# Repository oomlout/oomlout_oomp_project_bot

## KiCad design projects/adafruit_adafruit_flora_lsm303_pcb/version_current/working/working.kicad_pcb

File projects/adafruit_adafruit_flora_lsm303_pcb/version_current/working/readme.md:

# OOMP Project  
## Adafruit-Flora-LSM303-PCB  by adafruit  
  
oomp key: oomp_projects_flat_adafruit_adafruit_flora_lsm303_pcb  
(snippet of original readme)  
  
- Adafruit Flora LSM303 Sensor PCB  
<a href="http://www.adafruit.com/products/1247"><br/>  
Click here to purchase one from the Adafruit shop</a>  
  
Add motion and direction sensing to your wearable FLORA project with this high precision 3-axis Accelerometer+Compass sensor. Inside are two sensors, one is a classic 3-axis accelerometer, which can tell you which direction is down towards the Earth (by measuring gravity) or how fast the board is accelerating in 3D space. The other is a magnetometer that can sense where the strongest magnetic force is coming from, generally used to detect magnetic north. By combining this data you can then orient yourself.  
  
We based this sensor on the latest version of this popular sensor, the LSM303DLHC. The sensor has a digital (I2C) interface. Attaching it to the FLORA is simple: line up the sensor so its adjacent to the SDA/SCL pins and sew conductive thread from the 3V, SDA, SCL and GND pins. They line up perfectly so you will not have any crossed lines. You can only connect one of these sensors to your FLORA, but you can connect other I2C sensors/outputs by using the set of SCL/SDA pins on the opposite side.  
  
PCB files for Adafruit Flora LSM303 sensor. The format is EagleCAD schematic and board layout  
- https://www.adafruit.com/product/1247  
  
--- License  
  
Adafruit invests time and resources providing this open source design, please support Adafruit and open-source hardware by purchasing products   
  full source readme at [readme_src.md](readme_src.md)  
  
source repo at: [https://github.com/adafruit/Adafruit-Flora-LSM303-PCB](https://github.com/adafruit/Adafruit-Flora-LSM303-PCB)  
## Board  

## Schematic  

[schematic pdf](working_schematic.pdf)  
## Images

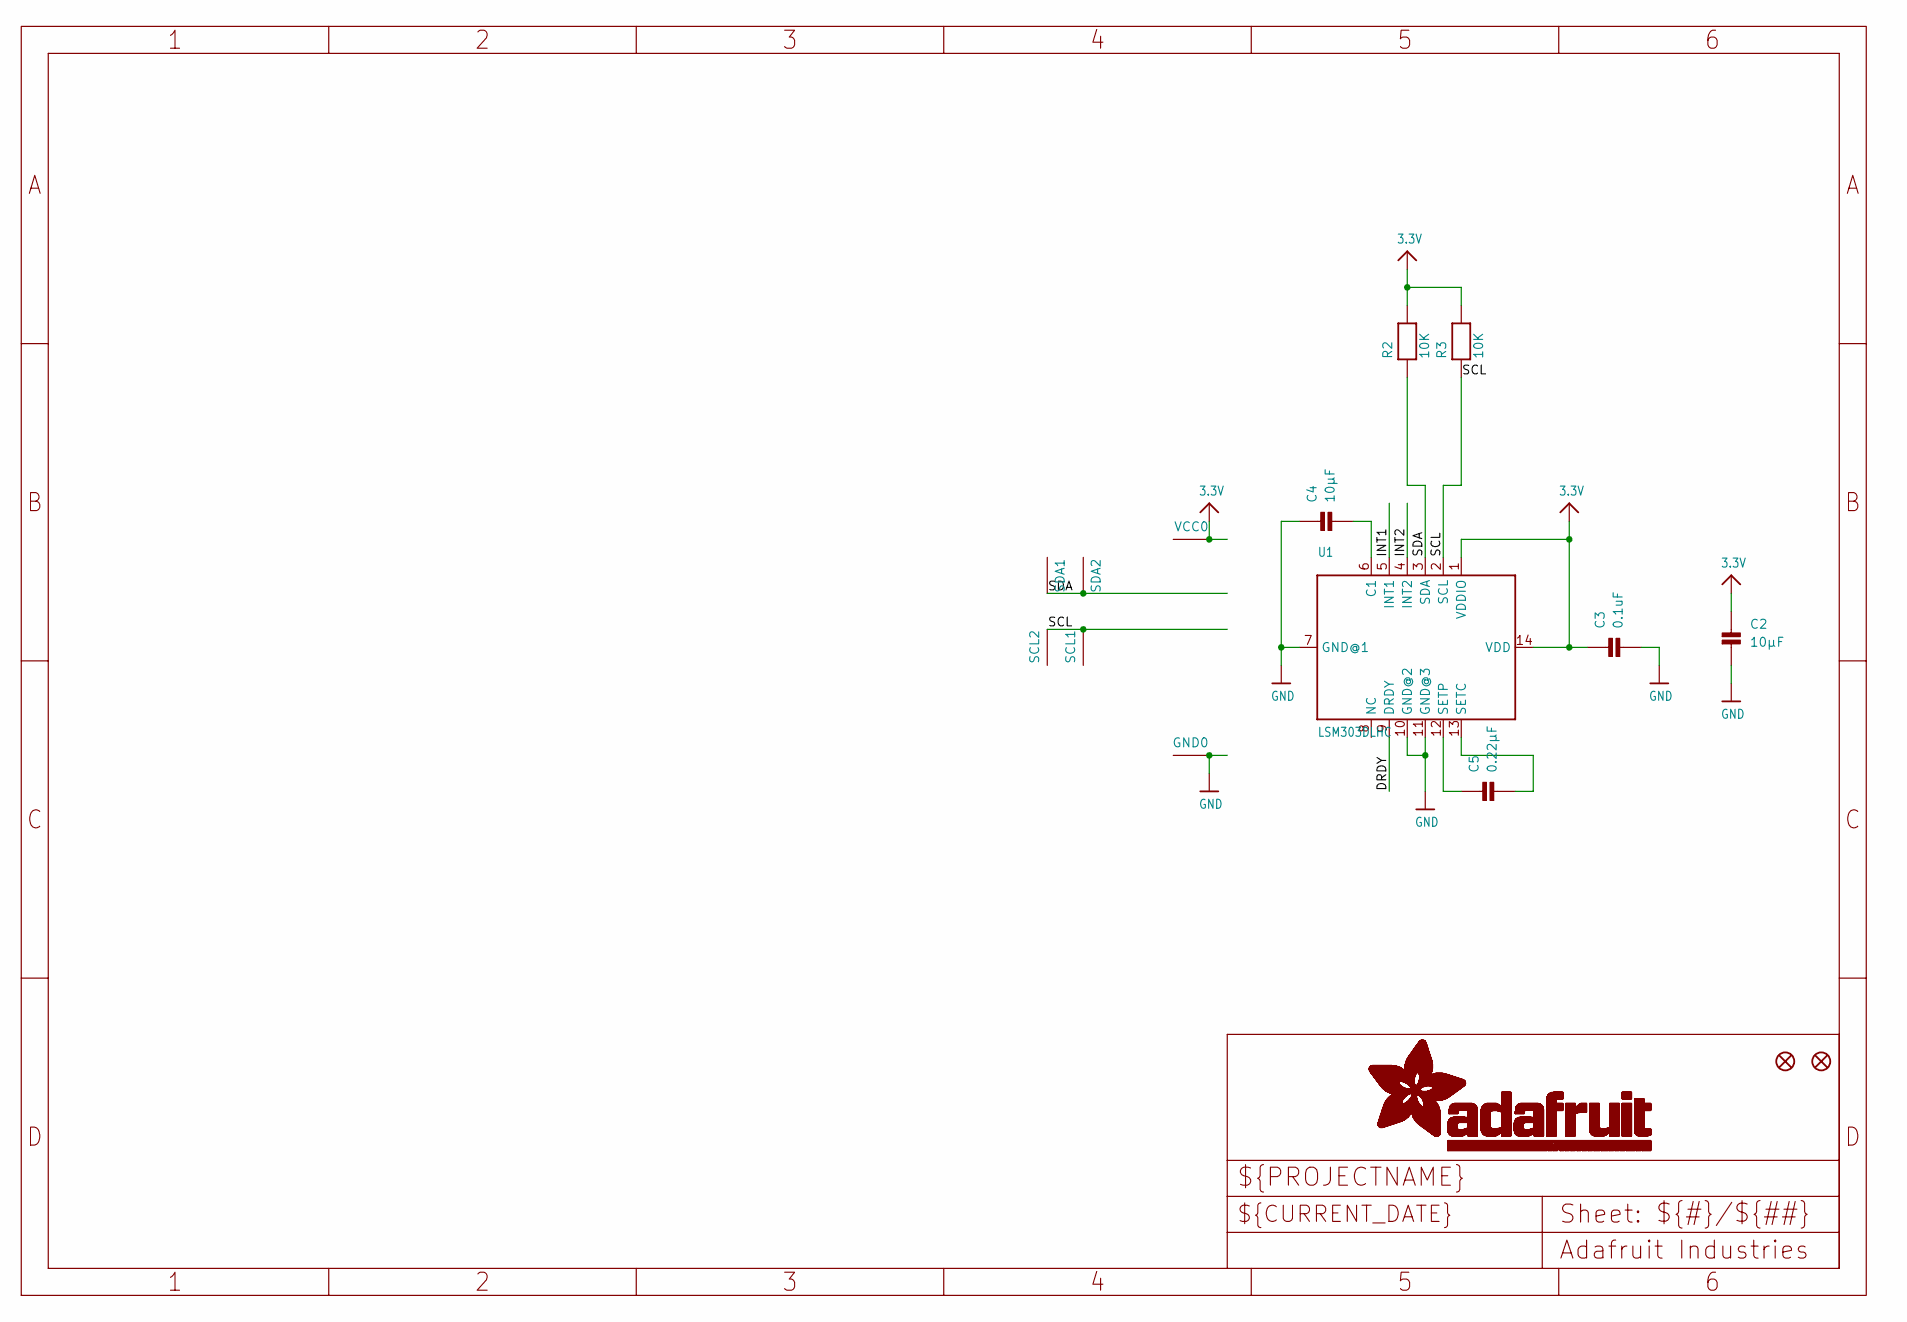
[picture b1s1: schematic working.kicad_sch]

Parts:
C2, C4: 10µF; _0805
C3: 0.1uF; _0805
C5: 0.22µF; _0805
FID1, FID2: FIDUCIAL""; FIDUCIAL_1MM
GND0: SEWTAP0.5IN; SEWINGTAP_0.5
R2, R3: 10K; _0805
SCL1, SCL2: SEWTAP0.5IN; SEWINGTAP_0.5
SDA1, SDA2: SEWTAP0.5IN; SEWINGTAP_0.5
U1: LSM303DLHC; LGA14
VCC0: SEWTAP0.5IN; SEWINGTAP_0.5

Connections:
3.3V: C2.1, C3.1, R2.2, R3.2, U1.1 (VDDIO), U1.14 (VDD), VCC0.TAP
DRDY: U1.9 (DRDY)
GND: C2.2, C3.2, C4.1, GND0.TAP, U1.7 (GND@1), U1.10 (GND@2), U1.11 (GND@3)
INT1: U1.5 (INT1)
INT2: U1.4 (INT2)
unnamed: C4.2, U1.6 (C1)
unnamed: C5.1, U1.12 (SETP)
unnamed: C5.2, U1.13 (SETC)
SCL: R3.1, SCL1.TAP, SCL2.TAP, U1.2 (SCL)
SDA: R2.1, SDA1.TAP, SDA2.TAP, U1.3 (SDA)

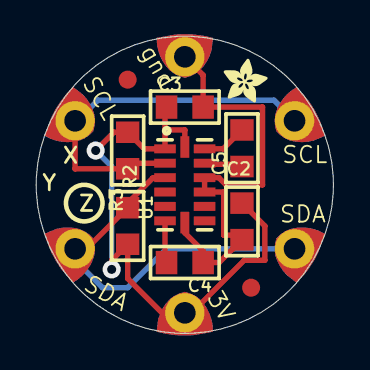
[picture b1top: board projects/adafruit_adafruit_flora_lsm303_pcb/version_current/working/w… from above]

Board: 2 copper layers, 16.5 x 16.5 mm, 16 parts (0 on the bottom side), 7 nets.

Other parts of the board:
U$4: ADAFRUIT_2.5MM

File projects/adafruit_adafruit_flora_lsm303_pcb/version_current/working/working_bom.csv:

Row,Description,Part,References,Value,Footprint,Quantity Per PCB,Status,Datasheet
1,,CAP_CERAMIC_0805,C3,0.1uF,_0805,1, ,
2,,CAP_CERAMIC_0805,C5,0.22µF,_0805,1, ,
3,,CAP_CERAMIC_0805,C2 C4,10µF,_0805,2, ,
4,,SEWTAP0.5IN,GND0 SCL1 SCL2 SDA1 SDA2 VCC0,SEWTAP0.5IN,SEWINGTAP_0.5,6, ,
5,,RESISTOR_0805,R2 R3,10K,_0805,2, ,
6,,LSM303DLHC,U1,LSM303DLHC,LGA14,1, ,





Project info:
Schematic:,working
Variant:,default
Revision:,
Date:,2023-08-02_17-08-33
KiCad Version:,7.0.6-7.0.6~ubuntu22.04.1
Statistics:
Component Groups:,6
Component Count:,13 (0 SMD/ 0 THT)
Fitted Components:,13 (0 SMD/ 0 THT)
Number of PCBs:,1
Total Components:,13

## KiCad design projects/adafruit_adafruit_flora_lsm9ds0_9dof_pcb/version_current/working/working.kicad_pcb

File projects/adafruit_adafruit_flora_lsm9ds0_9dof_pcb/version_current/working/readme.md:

# OOMP Project  
## Adafruit-Flora-LSM9DS0-9DOF-PCB  by adafruit  
  
oomp key: oomp_projects_flat_adafruit_adafruit_flora_lsm9ds0_9dof_pcb  
(snippet of original readme)  
  
- Adafruit Flora LSM9DS0 9DOF PCB  
<a href="http://www.adafruit.com/products/2020"><br/>  
Click here to purchase one from the Adafruit shop</a>  
  
Add motion, direction and orientation sensing to your wearable FLORA project with this high precision 9-DOF sensors. Inside are three sensors, one is a classic 3-axis accelerometer, which can tell you which direction is down towards the Earth (by measuring gravity) or how fast the board is accelerating in 3D space. The other is a 3-axis magnetometer that can sense where the strongest magnetic force is coming from, generally used to detect magnetic north.  The third is a 3-axis gyroscope that can measure spin and twist.  By combining this data you can REALLY orient yourself.  
  
When we saw the new LSM9DS0 from ST micro we thought - wow this could really make some wearables super smart. Design your own activity or motion tracker with all the data! The sensor has a digital (I2C) interface. Attaching it to the FLORA is simple: line up the sensor so its adjacent to the SDA/SCL pins and sew conductive thread from the 3V, SDA, SCL and GND pins. They line up perfectly so you will not have any crossed lines. You can only connect one of these sensors to your FLORA, but you can connect other I2C sensors/outputs by using the set of SCL/SDA pins on the opposite side.  
  
PCB files for Adafruit Flora LSM9DS0 9-DOF Sensor PCB. The format is EagleCAD schematic and board layout  
- https://www.adafruit.com/pr  
  full source readme at [readme_src.md](readme_src.md)  
  
source repo at: [https://github.com/adafruit/Adafruit-Flora-LSM9DS0-9DOF-PCB](https://github.com/adafruit/Adafruit-Flora-LSM9DS0-9DOF-PCB)  
## Board  

## Schematic  

[schematic pdf](working_schematic.pdf)  
## Images

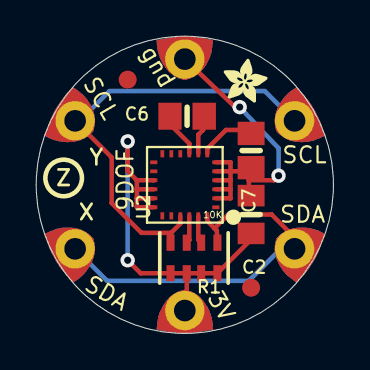
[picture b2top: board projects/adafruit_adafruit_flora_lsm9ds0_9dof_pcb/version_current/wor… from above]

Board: 2 copper layers, 16.5 x 16.5 mm, 14 parts (0 on the bottom side), 9 nets.

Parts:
C2: 10µF; 0805_10MGAP
C6: 0.22uF; 0805-NO
C7: 10uF; 0805-NO
FID1, FID2: FIDUCIAL""; FIDUCIAL_1MM
GND0: SEWTAP0.5IN; SEWINGTAP_0.5
R1: 10K; RESPACK_4X0603
SCL1, SCL2: SEWTAP0.5IN; SEWINGTAP_0.5
SDA1, SDA2: SEWTAP0.5IN; SEWINGTAP_0.5
U2: LSM9DS0TR; LGA24_4X4MM
U$4: ADAFRUIT_2.5MM
VCC0: SEWTAP0.5IN; SEWINGTAP_0.5

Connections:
3.3V: C2.1, R1.5, R1.6, R1.7, R1.8, U2.15, U2.16, U2.17, U2.18, VCC0.TAP
GND: C2.2, C7.2, GND0.TAP, U2.2, U2.3, U2.4, U2.5, U2.6
unnamed: C6.1, U2.8
unnamed: C6.2, U2.9
unnamed: C7.1, U2.7
SA0_G: R1.3, U2.22
SA0_XM: R1.2, U2.23
SCL: R1.4, SCL1.TAP, SCL2.TAP, U2.21
SDA: R1.1, SDA1.TAP, SDA2.TAP, U2.24

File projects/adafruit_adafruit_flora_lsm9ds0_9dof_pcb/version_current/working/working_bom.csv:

Row,Description,Part,References,Value,Footprint,Quantity Per PCB,Status,Datasheet
1,,CAP_CERAMIC0805-NOOUTLINE,C6,0.22uF,0805-NO,1, ,
2,,CAP_CERAMIC0805_10MGAP,C2,10µF,0805_10MGAP,1, ,
3,,CAP_CERAMIC0805-NOOUTLINE,C7,10uF,0805-NO,1, ,
4,,SEWTAP0.5IN,GND0 SCL1 SCL2 SDA1 SDA2 VCC0,SEWTAP0.5IN,SEWINGTAP_0.5,6, ,
5,,RESISTOR_4PACK_US,R1,10K,RESPACK_4X0603,1, ,
6,,LSM9DS0,U2,LSM9DS0TR,LGA24_4X4MM,1, ,





Project info:
Schematic:,working
Variant:,default
Revision:,
Date:,2023-08-02_17-08-33
KiCad Version:,7.0.6-7.0.6~ubuntu22.04.1
Statistics:
Component Groups:,6
Component Count:,11 (0 SMD/ 0 THT)
Fitted Components:,11 (0 SMD/ 0 THT)
Number of PCBs:,1
Total Components:,11

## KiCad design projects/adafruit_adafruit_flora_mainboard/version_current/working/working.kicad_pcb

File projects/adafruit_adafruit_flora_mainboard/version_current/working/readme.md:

# OOMP Project  
## Adafruit-Flora-Mainboard  by adafruit  
  
oomp key: oomp_projects_flat_adafruit_adafruit_flora_mainboard  
(snippet of original readme)  
  
- Adafruit Flora Mainboard PCB Files  
<a href="http://www.adafruit.com/products/659"><br/>  
Click here to purchase one from the Adafruit shop</a>  
  
FLORA is Adafruit's fully-featured wearable electronics platform. It's a round, sewable, Arduino-compatible microcontroller designed to empower amazing wearables projects.FLORA comes with Adafruit's support, tutorials and projects. Check out dozens of FLORA tutorials on the Adafruit Learning System, with more added all the time!  
  
The FLORA is small (1.75" diameter, weighing 4.4 grams). The FLORA family also has the best stainless steel threads, sensors, GPS modules and chainable LED NeoPixels, perfect accessories for the FLORA main board.   
  
The FLORA has built-in USB support. Built in USB means you plug it in to program it, it just shows up - all you need is a Micro-B USB cable, no additional purchases are needed! We have a modified version of the Arduino IDE so Mac & Windows users can get started fast - or with the new 1.6.4+ Arduino IDE, it takes only a few seconds to add Flora-support. The FLORA has USB HID support, so it can act like a mouse or keyboard to attach directly to computers.  
  
This is the PCB for the Adafruit Flora Mainboard. The format is EagleCAD schematic and board layout  
- http://adafruit.com/products/659  
  
--- License  
  
Adafruit invests time and resources providing this open source design, please support Adafruit and open-source hardware by purchasing products from [Ad  
  full source readme at [readme_src.md](readme_src.md)  
  
source repo at: [https://github.com/adafruit/Adafruit-Flora-Mainboard](https://github.com/adafruit/Adafruit-Flora-Mainboard)  
## Board  

## Schematic  

[schematic pdf](working_schematic.pdf)  
## Images

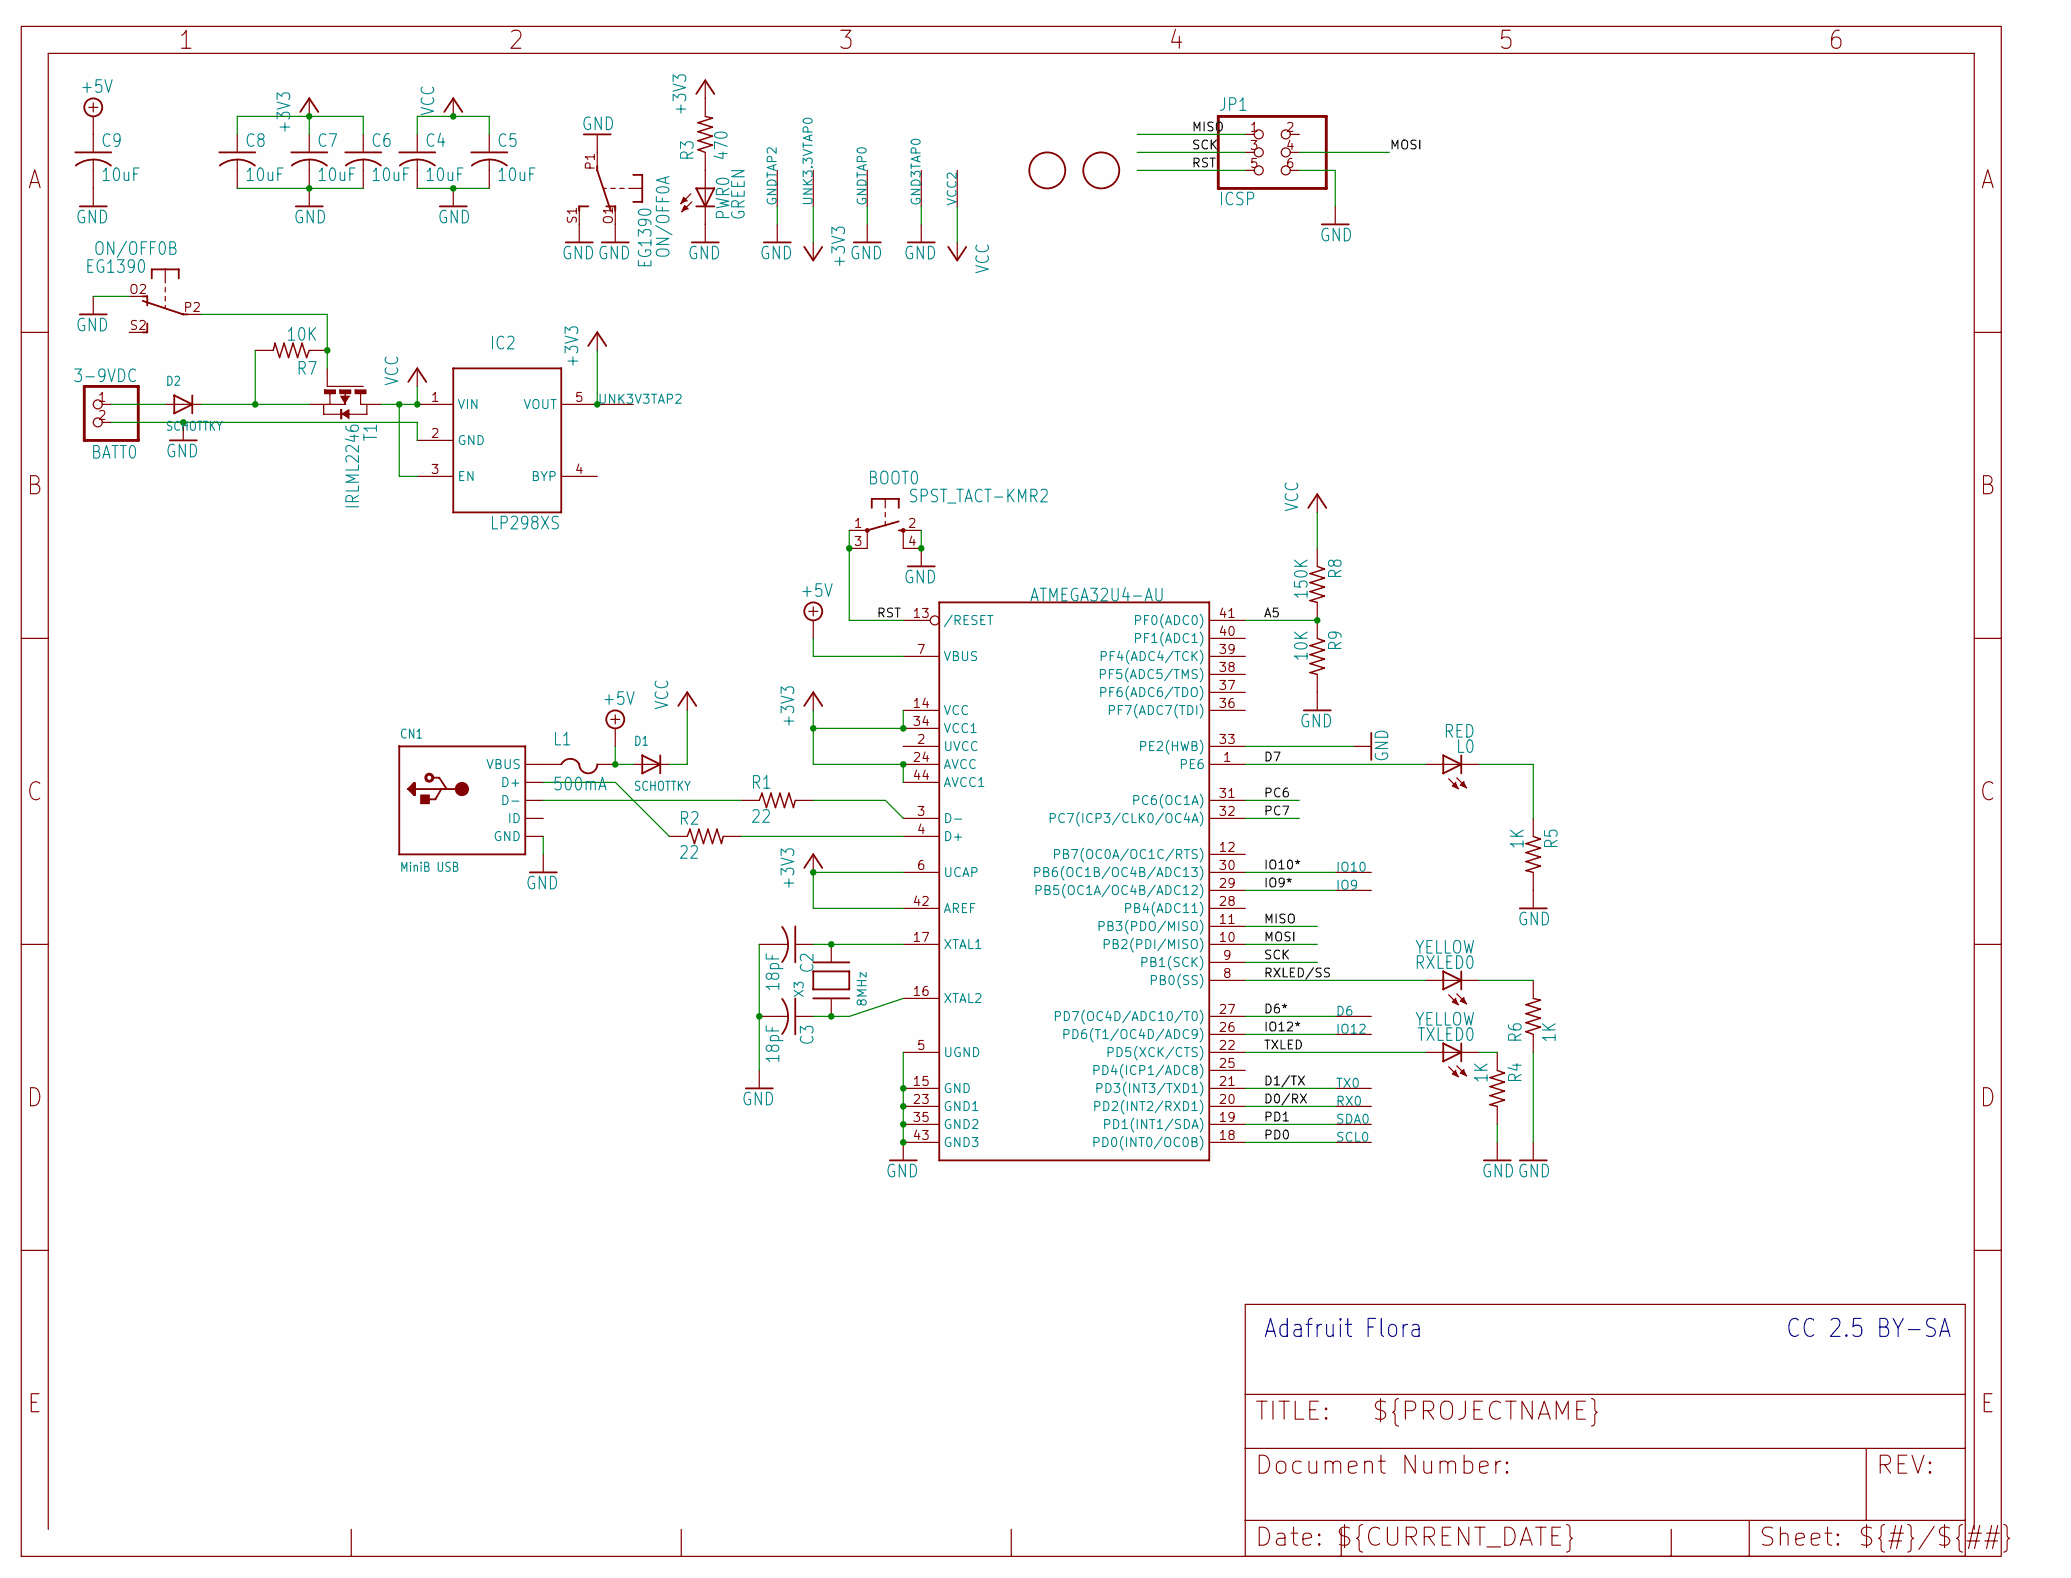
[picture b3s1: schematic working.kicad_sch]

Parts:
BATT0: 3-9VDC; JST-PH-2-SMT-RA
BOOT0: SPST_TACT-KMR2; KMR2
C2, C3: 18pF; C0805K
C4, C5, C6, C7, C8, C9: 10uF; C0805K
CN1: MiniB USB; USB-MINIB_LARGER
D1, D2: SCHOTTKY; SOD-123
D6: SEWTAP-2.0IN; SEWINGTAP_2.0
GND3TAP0: SEWTAP-2.0IN; SEWINGTAP_2.0
GNDTAP0, GNDTAP2: SEWTAP-2.0IN; SEWINGTAP_2.0
IC1: ATMEGA32U4-AU; TQFP44
IC2: LP298XS; SOT23-5L
IO9, IO10, IO12: SEWTAP-2.0IN; SEWINGTAP_2.0
JP1: ICSP; 2X03
L0: RED; CHIPLED_0805
L1: 500mA; R1206
ON/OFF0: EG1390
PWR0: GREEN; CHIPLED_0805
R1, R2: 22; R0805
R3: 470; R0805
R4, R5, R6: 1K; R0805
R7, R9: 10K; R0805
R8: 150K; R0805
RX0: SEWTAP-2.0IN; SEWINGTAP_2.0
RXLED0: YELLOW; CHIPLED_0805
SCL0: SEWTAP-2.0IN; SEWINGTAP_2.0
SDA0: SEWTAP-2.0IN; SEWINGTAP_2.0
T1: IRLML2246; SOT-23
TX0: SEWTAP-2.0IN; SEWINGTAP_2.0
TXLED0: YELLOW; CHIPLED_0805
U$2, U$6: FIDUCIAL; FIDUCIAL_1MM
UNK3.3VTAP0, UNK3V3TAP2: SEWTAP-2.0IN; SEWINGTAP_2.0
VCC2: SEWTAP-2.0IN; SEWINGTAP_2.0
X3: 8MHz; NX5032

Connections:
+3V3: C6.1, C7.1, C8.1, IC1.6 (UCAP), IC1.14 (VCC), IC1.24 (AVCC), IC1.34 (VCC1), IC1.42 (AREF), IC1.44 (AVCC1), IC2.5 (VOUT), R3.2, UNK3.3VTAP0.P$1, UNK3V3TAP2.P$1
+5V: C9.1, D1.A, IC1.7 (VBUS), L1.2
A5: IC1.41 (PF0(ADC0)), R8.2, R9.1
D0/RX: IC1.20 (PD2(INT2/RXD1)), RX0.P$1
D1/TX: IC1.21 (PD3(INT3/TXD1)), TX0.P$1
D6*: D6.P$1, IC1.27 (PD7(OC4D/ADC10/T0))
D7: IC1.1 (PE6), L0.A
GND: BATT0.2 (1), BOOT0.2 (S), BOOT0.4 (S1), C2.2, C3.2, C4.2, C5.2, C6.2, C7.2, C8.2, C9.2, CN1.GND, GND3TAP0.P$1, GNDTAP0.P$1, GNDTAP2.P$1, IC1.5 (UGND), IC1.15 (GND), IC1.23 (GND1), IC1.33 (PE2(HWB)), IC1.35 (GND2), IC1.43 (GND3), IC2.2 (GND), JP1.6, ON/OFF0.O1 (O), ON/OFF0.O2 (O), ON/OFF0.P1, ON/OFF0.S1 (S), PWR0.C, R4.2, R5.2, R6.1, R9.2
IO9*: IC1.29 (PB5(OC1A/OC4B/ADC12)), IO9.P$1
IO10*: IC1.30 (PB6(OC1B/OC4B/ADC13)), IO10.P$1
IO12*: IC1.26 (PD6(T1/OC4D/ADC9)), IO12.P$1
MISO: IC1.11 (PB3(PDO/MISO)), JP1.1
MOSI: IC1.10 (PB2(PDI/MISO)), JP1.4
unnamed: PWR0.A, R3.1
unnamed: CN1.D+, R2.1
unnamed: IC1.3 (D-), R1.2
unnamed: IC1.4 (D+), R2.2
unnamed: CN1.D-, R1.1
unnamed: D2.C, R7.2, T1.2 (S)
unnamed: BATT0.1 (2), D2.A
unnamed: C2.1, IC1.17 (XTAL1), X3.P$2
unnamed: C3.1, IC1.16 (XTAL2), X3.P$1
unnamed: L0.C, R5.1
unnamed: R4.1, TXLED0.C
unnamed: R6.2, RXLED0.C
unnamed: ON/OFF0.P2, R7.1, T1.3 (G)
PC6: IC1.31 (PC6(OC1A))
PC7: IC1.32 (PC7(ICP3/CLK0/OC4A))
PD0: IC1.18 (PD0(INT0/OC0B)), SCL0.P$1
PD1: IC1.19 (PD1(INT1/SDA)), SDA0.P$1
RST: BOOT0.1, BOOT0.3 (P1), IC1.13 (/RESET), JP1.5
RXLED/SS: IC1.8 (PB0(SS)), RXLED0.A
SCK: IC1.9 (PB1(SCK)), JP1.3
TXLED: IC1.22 (PD5(XCK/CTS)), TXLED0.A
VBUS: CN1.VBUS, L1.1
VCC: C4.1, C5.1, D1.C, IC2.1 (VIN), IC2.3 (EN), R8.1, T1.1 (D), VCC2.P$1

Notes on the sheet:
CC 2.5 BY-SA
Adafruit Flora

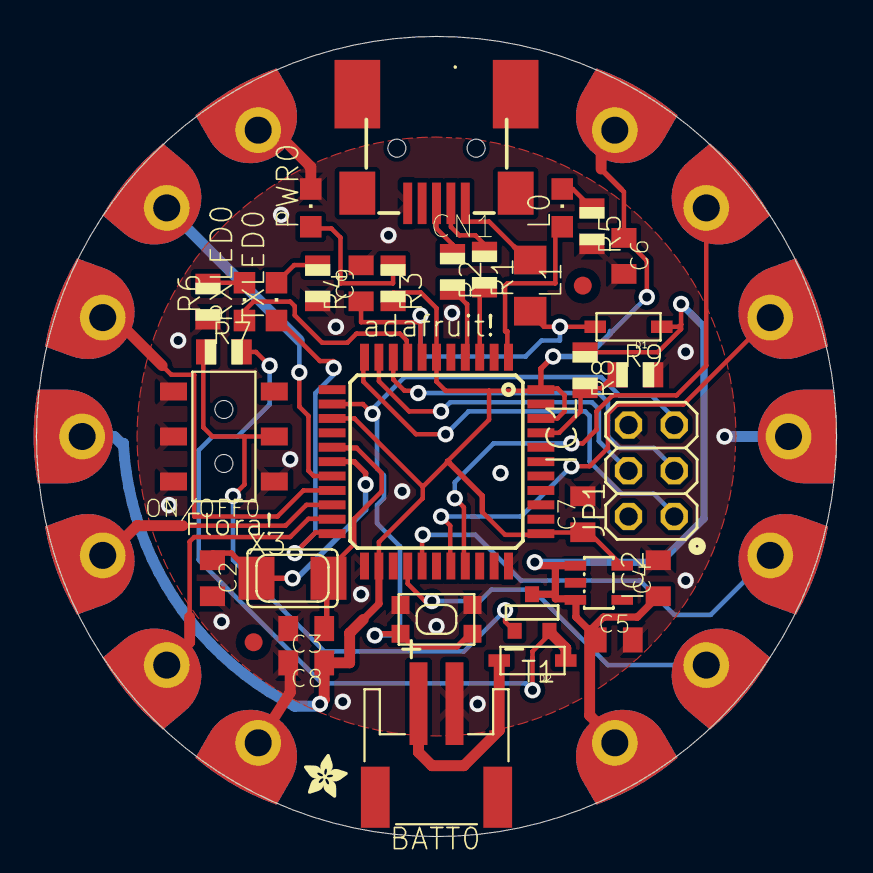
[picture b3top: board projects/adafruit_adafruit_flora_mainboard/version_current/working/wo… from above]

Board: 16 copper layers, 44.5 x 44.5 mm, 51 parts (1 on the bottom side), 34 nets.

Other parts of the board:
U$3: ADAFRUIT_2.5MM
U$4: FLORAMED

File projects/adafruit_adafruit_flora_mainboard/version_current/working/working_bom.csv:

Row,Description,Part,References,Value,Footprint,Quantity Per PCB,Status,Datasheet
1,,JST_2PIN-SMT-RA,BATT0,3-9VDC,JST-PH-2-SMT-RA,1, ,
2,,SPST_TACT-KMR2,BOOT0,SPST_TACT-KMR2,KMR2,1, ,
3,,C-USC0805K,C2 C3,18pF,C0805K,2, ,
4,,C-USC0805K,C4 C5 C6 C7 C8 C9,10uF,C0805K,6, ,
5,,USBMINIBLARGE,CN1,MiniB USB,USB-MINIB_LARGER,1, ,
6,,DIODESOD-123,D1 D2,SCHOTTKY,SOD-123,2, ,
7,,SEWTAP-2.0IN,D6 GND3TAP0 GNDTAP0 GNDTAP2 IO9 IO10 IO12 RX0 SCL0 SDA0 TX0 UNK3.3VTAP0 UNK3V3TAP2 VCC2,SEWTAP-2.0IN,SEWINGTAP_2.0,14, ,
8,,ATMEGA32U4-AU,IC1,ATMEGA32U4-AU,TQFP44,1, ,
9,,LP298XS,IC2,LP298XS,SOT23-5L,1, ,
10,,PINHD-2X3,JP1,ICSP,2X03,1, ,
11,,PTCFUSE-1206,L1,500mA,R1206,1, ,
12,,LEDCHIPLED_0805,L0,RED,CHIPLED_0805,1, ,
13,,DPDT-EG1390,ON/OFF0,EG1390,EG1390,1, ,
14,,LEDCHIPLED_0805,PWR0,GREEN,CHIPLED_0805,1, ,
15,,R-US_R0805,R1 R2,22,R0805,2, ,
16,,R-US_R0805,R3,470,R0805,1, ,
17,,R-US_R0805,R4 R5 R6,1K,R0805,3, ,
18,,R-US_R0805,R7 R9,10K,R0805,2, ,
19,,R-US_R0805,R8,150K,R0805,1, ,
20,,LEDCHIPLED_0805,RXLED0 TXLED0,YELLOW,CHIPLED_0805,2, ,
21,,PMOSSOT23,T1,IRLML2246,SOT-23,1, ,
22,,XTALNX5032,X3,8MHz,NX5032,1, ,





Project info:
Schematic:,working
Variant:,default
Revision:,
Date:,2023-08-02_17-08-33
KiCad Version:,7.0.6-7.0.6~ubuntu22.04.1
Statistics:
Component Groups:,22
Component Count:,47 (0 SMD/ 0 THT)
Fitted Components:,47 (0 SMD/ 0 THT)
Number of PCBs:,1
Total Components:,47

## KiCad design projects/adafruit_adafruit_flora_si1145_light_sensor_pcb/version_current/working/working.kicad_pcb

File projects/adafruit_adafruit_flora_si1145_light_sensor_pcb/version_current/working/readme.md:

# Adafruit-Flora-Si1145-Light-Sensor-PCB by adafruit  
This is a harvested standardized copy of a project from github.  
The original project can be found at:  
https://github.com/adafruit/Adafruit-Flora-Si1145-Light-Sensor-PCB  
Please consult that link for additional, details, files, and license information.  
Note: It was auto harvested and if the original repo had more than one board file or anything out of the ordinary the files here are likely not representative.

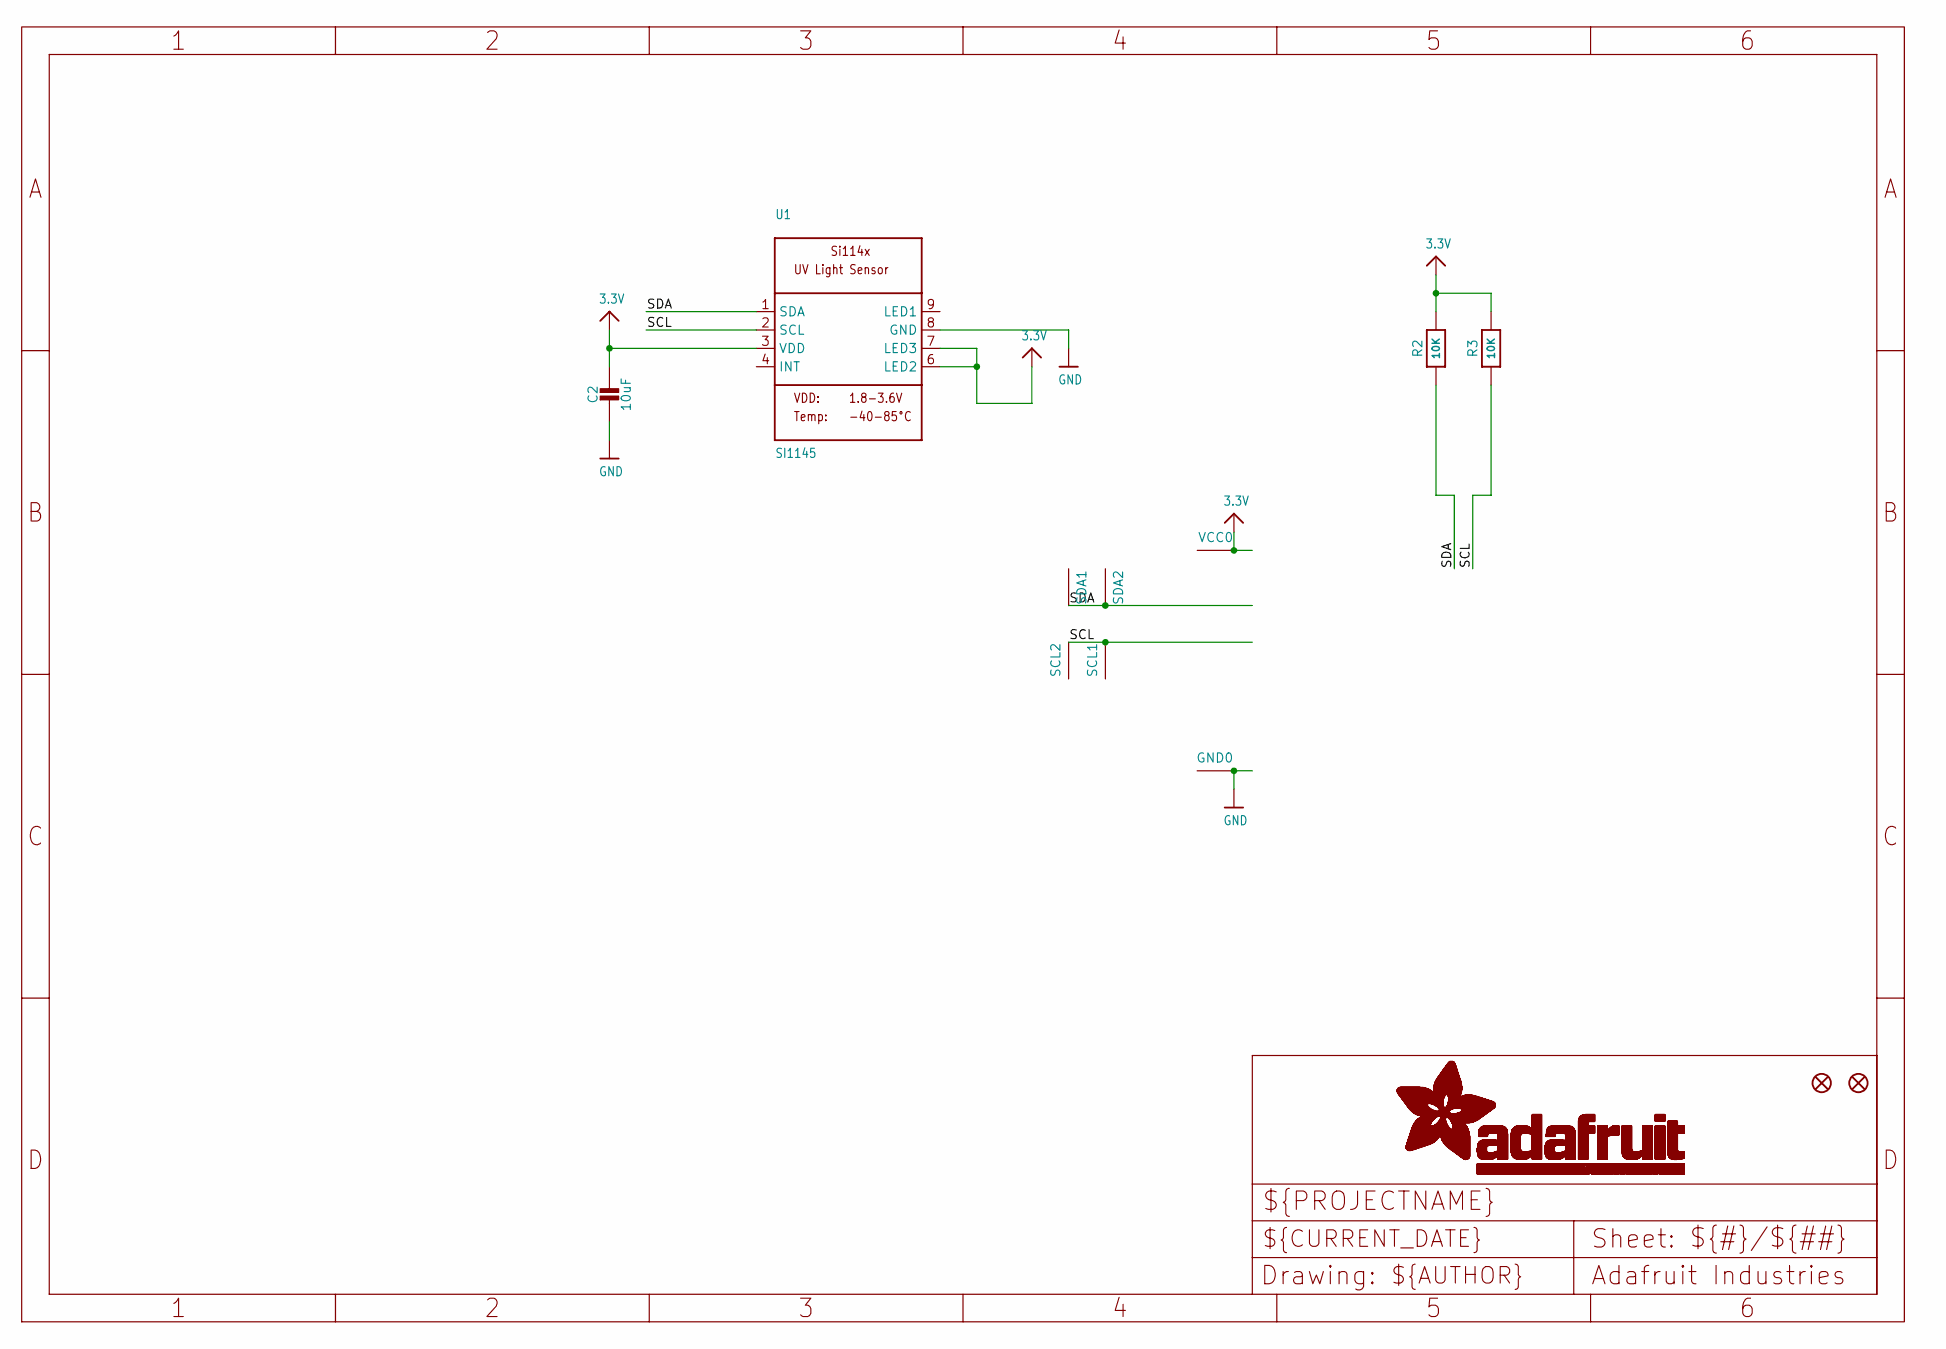
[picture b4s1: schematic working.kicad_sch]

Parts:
C2: 10uF; 0805-NO
FID1, FID2: FIDUCIAL""; FIDUCIAL_1MM
GND0: SEWTAP0.5IN; SEWINGTAP_0.5
R2, R3: 10K; 0805-NO
SCL1, SCL2: SEWTAP0.5IN; SEWINGTAP_0.5
SDA1, SDA2: SEWTAP0.5IN; SEWINGTAP_0.5
U1: SI1145; SI114X
VCC0: SEWTAP0.5IN; SEWINGTAP_0.5

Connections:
3.3V: C2.1, R2.2, R3.2, U1.3 (VDD), U1.6 (LED2), U1.7 (LED3), VCC0.TAP
GND: C2.2, GND0.TAP, U1.8 (GND)
SCL: R3.1, SCL1.TAP, SCL2.TAP, U1.2 (SCL)
SDA: R2.1, SDA1.TAP, SDA2.TAP, U1.1 (SDA)

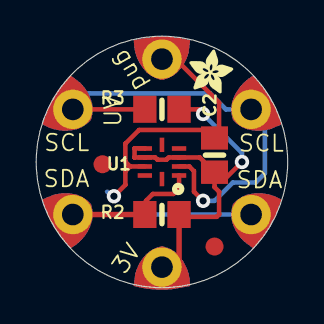
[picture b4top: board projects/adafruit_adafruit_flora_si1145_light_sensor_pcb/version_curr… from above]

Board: 2 copper layers, 14.0 x 14.0 mm, 14 parts (1 on the bottom side), 4 nets.

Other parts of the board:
U$3, U$4: ADAFRUIT_2.5MM

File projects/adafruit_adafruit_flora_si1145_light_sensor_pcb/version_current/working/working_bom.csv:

Row,Description,Part,References,Value,Footprint,Quantity Per PCB,Status,Datasheet
1,,CAP_CERAMIC0805-NOOUTLINE,C2,10uF,0805-NO,1, ,
2,,SEWTAP0.5IN,GND0 SCL1 SCL2 SDA1 SDA2 VCC0,SEWTAP0.5IN,SEWINGTAP_0.5,6, ,
3,,RESISTOR0805_NOOUTLINE,R2 R3,10K,0805-NO,2, ,
4,,SI114X,U1,SI1145,SI114X,1, ,





Project info:
Schematic:,working
Variant:,default
Revision:,
Date:,2023-08-02_17-08-33
KiCad Version:,7.0.6-7.0.6~ubuntu22.04.1
Statistics:
Component Groups:,4
Component Count:,10 (0 SMD/ 0 THT)
Fitted Components:,10 (0 SMD/ 0 THT)
Number of PCBs:,1
Total Components:,10

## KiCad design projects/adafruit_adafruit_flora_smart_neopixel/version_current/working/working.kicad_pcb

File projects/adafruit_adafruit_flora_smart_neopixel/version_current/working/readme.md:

# OOMP Project  
## Adafruit-Flora-Smart-NeoPixel  by adafruit  
  
oomp key: oomp_projects_flat_adafruit_adafruit_flora_smart_neopixel  
(snippet of original readme)  
  
- PCB for the Adafruit Flora Smart NeoPixels  
  
<a href="http://www.adafruit.com/products/1060"><br/>Click here to purchase one from the Adafruit shop</a>  
  
__Format is EagleCAD schematic and board layout__  
  
What's a wearable project without LEDs? Our favorite part of the Flora platform is these tiny smart pixels. Designed specifically for wearables, [we found the brightest RGB LEDs available (an eye-blistering ~3800mcd)](http://adafruit.com/products/619) and paired them with a constant-current driver chip that sits on the back. The pixels are chainable - so you only need 1 pin/wire to control as many LEDs as you like. They're easy to sew, and the chainable design means no crossed threads.  
  
__This is the first/original version of the Flora NeoPixels, which runs at at 'low speed' 400KHz communication.__ Unfortunately they are not forward-compatible with [the fully-integrated 'high speed' (800KHz) Flora NeoPixel V2's](http://www.adafruit.com/products/1260). If you have a project that already uses high speed pixels, and you want to attach more pixels to the chain, [you will need to purchase version 2's](http://www.adafruit.com/products/1260) as these are not cross-compatible. __If you don't have any pixels in your project yet, [we suggest purchasing v2 pixels](http://www.adafruit.com/products/1260) as they are lower cost and v1's will eventually be discontinued.__  
  
These pixels have full 24-bit color ability with PWM taken care of   
  full source readme at [readme_src.md](readme_src.md)  
  
source repo at: [https://github.com/adafruit/Adafruit-Flora-Smart-NeoPixel](https://github.com/adafruit/Adafruit-Flora-Smart-NeoPixel)  
## Board  

## Schematic  

[schematic pdf](working_schematic.pdf)  
## Images

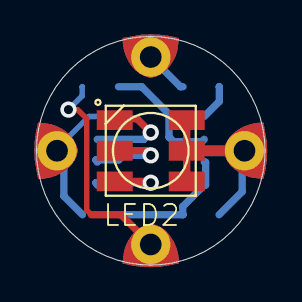
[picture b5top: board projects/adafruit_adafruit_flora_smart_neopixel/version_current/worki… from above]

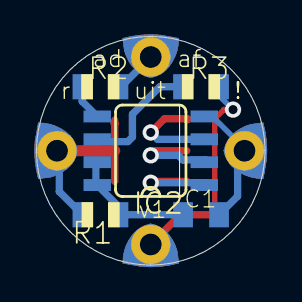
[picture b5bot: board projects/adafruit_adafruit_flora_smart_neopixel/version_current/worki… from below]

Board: 16 copper layers, 12.7 x 12.7 mm, 10 parts (5 on the bottom side), 10 nets.

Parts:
C1: 1uF; C0805K
DATA_INPUT0: SEWTAP0.5IN; SEWINGTAP_0.5
DATA_OUTPUT0: SEWTAP0.5IN; SEWINGTAP_0.5
GND0: SEWTAP0.5IN; SEWINGTAP_0.5
IC2: WS2811-SOP8; SO08-SKINNYPADS
LED2: RGBLED5050
R1: 1.0K; R0805
R2, R3: 22; R0805
VDD0: SEWTAP0.5IN; SEWINGTAP_0.5

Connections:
GND: C1.2, GND0.TAP, IC2.4
unnamed: IC2.3, LED2.4
unnamed: IC2.2, LED2.5
unnamed: IC2.1, LED2.6
unnamed: IC2.6, R3.1
unnamed: IC2.5, R2.1
unnamed: DATA_INPUT0.TAP, R3.2
unnamed: DATA_OUTPUT0.TAP, R2.2
unnamed: C1.1, IC2.7, IC2.8, R1.1
VDD: LED2.1, LED2.2, LED2.3, R1.2, VDD0.TAP

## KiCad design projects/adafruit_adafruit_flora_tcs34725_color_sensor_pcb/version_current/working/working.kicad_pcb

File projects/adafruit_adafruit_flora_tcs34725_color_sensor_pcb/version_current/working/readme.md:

# Adafruit-Flora-TCS34725-Color-Sensor-PCB by adafruit  
This is a harvested standardized copy of a project from github.  
The original project can be found at:  
https://github.com/adafruit/Adafruit-Flora-TCS34725-Color-Sensor-PCB  
Please consult that link for additional, details, files, and license information.  
Note: It was auto harvested and if the original repo had more than one board file or anything out of the ordinary the files here are likely not representative.

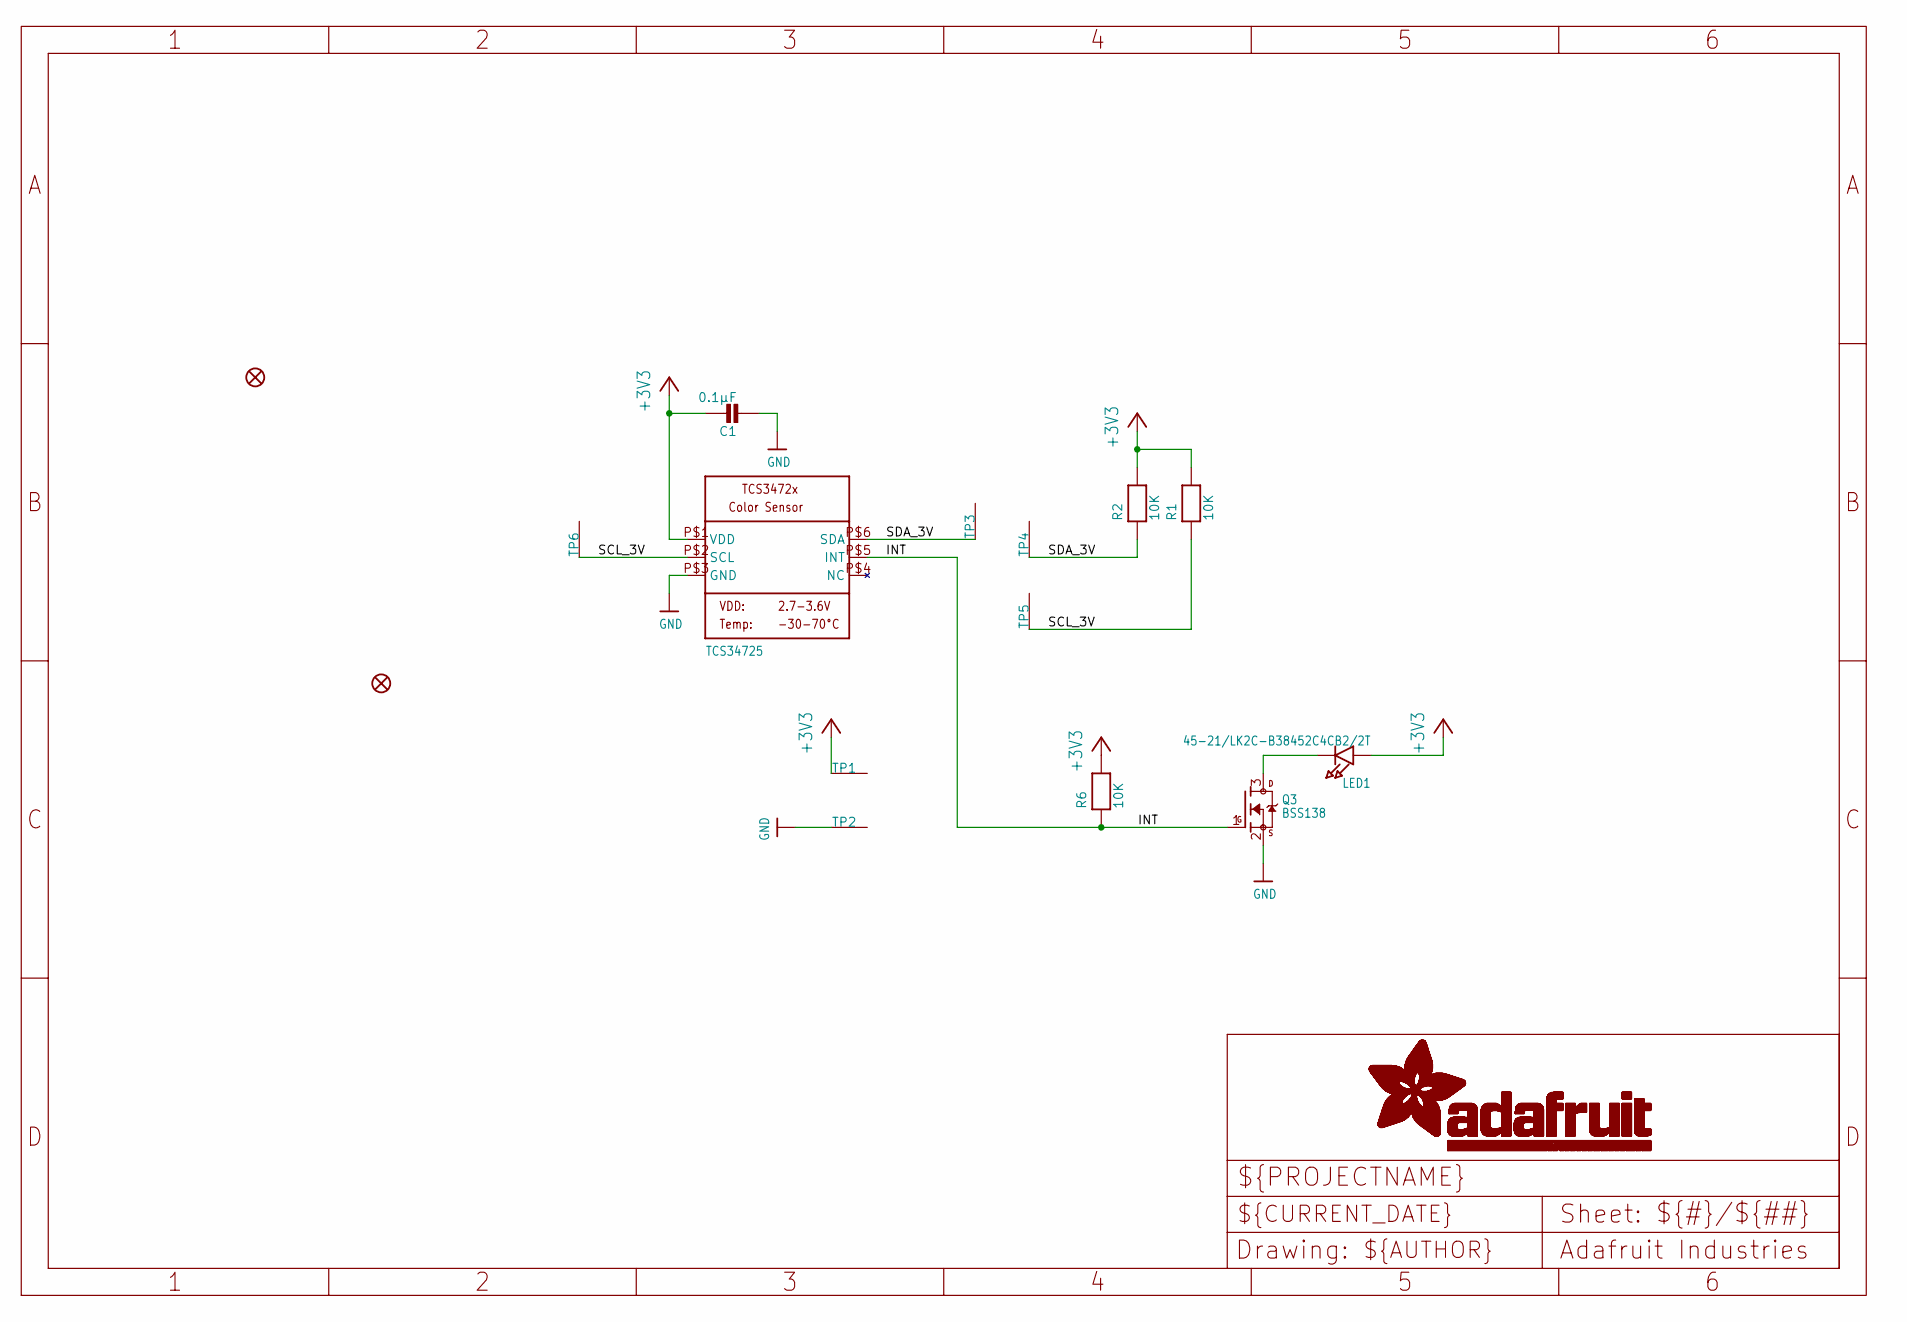
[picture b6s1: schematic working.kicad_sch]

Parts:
C1: 0.1µF; _0805
FID1, FID2: FIDUCIAL""; FIDUCIAL_1MM
LED1: 45-21/LK2C-B38452C4CB2/2T; EVERLIGHT_45-21
Q3: BSS138; SOT23-WIDE
R1, R2, R6: 10K; _0805
TP1, TP2, TP3, TP4, TP5, TP6: SEWTAP0.5IN; SEWINGTAP_0.5
U1: TCS34725; TCS3472_FN6

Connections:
+3V3: C1.1, LED1.A, R1.2, R2.2, R6.2, TP1.TAP, U1.P$1 (VDD)
GND: C1.2, Q3.2 (S), TP2.TAP, U1.P$3 (GND)
INT: Q3.1 (G), R6.1, U1.P$5 (INT)
unnamed: LED1.K (C), Q3.3 (D)
SCL_3V: R1.1, TP5.TAP, TP6.TAP, U1.P$2 (SCL)
SDA_3V: R2.1, TP3.TAP, TP4.TAP, U1.P$6 (SDA)

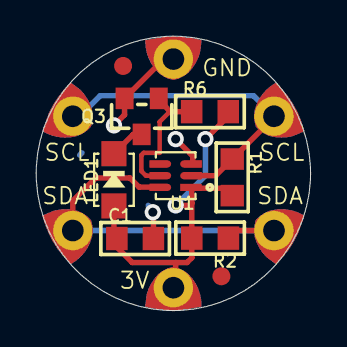
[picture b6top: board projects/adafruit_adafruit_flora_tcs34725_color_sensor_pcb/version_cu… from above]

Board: 2 copper layers, 15.2 x 15.2 mm, 16 parts (1 on the bottom side), 6 nets.

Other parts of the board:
U$8: ADAFRUIT_3.5MM
